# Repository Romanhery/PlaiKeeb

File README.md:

<h1>Plai-Keeb</h1>
Plai Keeb is a custom keyboard 75 % exploded keyboard with a rotary encoder and macro keys.
<h2>Features:</h2>
<ul>
   <li>Switched Rotary Encoder for volume control</li>
   <li>4 macro keys</li>
   <li>Candy Holder</li>
</ul>
<h2>PCB:</h2>
   <h2>Schematic</h2>
   
   <h2>PCB</h2>
   
   <p>Made in <a href="https://www.kicad.org/">Ki-CAD</a></p> 

<h2>CAD:</h2>
   <p>Everything is held together by using 6 M3 Bolts and heated inserts.</p>
   <p>It has 2 printed pieces and a plate to cover the electronics and house them.</p>
   <p>Made in Fusion 360</p>

<h2>Firmware:</h2>
   <p>Made with <a href="https://github.com/KMKfw/kmk_firmware">KMK</a> firmware</p> 
   <h3>Features</h3>
   <li>Volume control if you twist the rotary encoder and if you press the encoder to mute</li>
   <li>It has macros for any shorcut you want!</li>
   
<h2>BOM:</h2>
<p>Everything you need to make this macro pad is here!</p>
<ul>
    <li>9x Cherry MX Switches</li>
    <li>9x DSA Keycaps</li>
    <li>5x M3x5x4 Heatset inserts</li>
    <li>4x M3x16mm SHCS Bolts</li>
    <li>9x 1N4148 DO-35 Diodes.</li>
    <li>1x 0.91" OLED Display</li>
    <li>1x EC11 Rotary Encoder</li>
    <li>1x XIAO RP2040</li>
    <li>1x Case (2 printed parts)</li>
   <a href="https://docs.google.com/spreadsheets/d/1uIeMTGPOrdSAiFDxR4G393WpXhlTQVRrd_AwqsaPwl4/edit?usp=sharing">BOM HERE WITH LINKS</a>
</ul>
<h2>Acknowledgements</h2> 

* [Keeb](https://github.com/hackclub/hackpad/tree/main/cad/orpheuspad)
* [Void Pointer](https://github.com/Mirai-09/Keybie-Hackpads)
## Authors
- [@Romanhery](https://github.com/Romanhery)

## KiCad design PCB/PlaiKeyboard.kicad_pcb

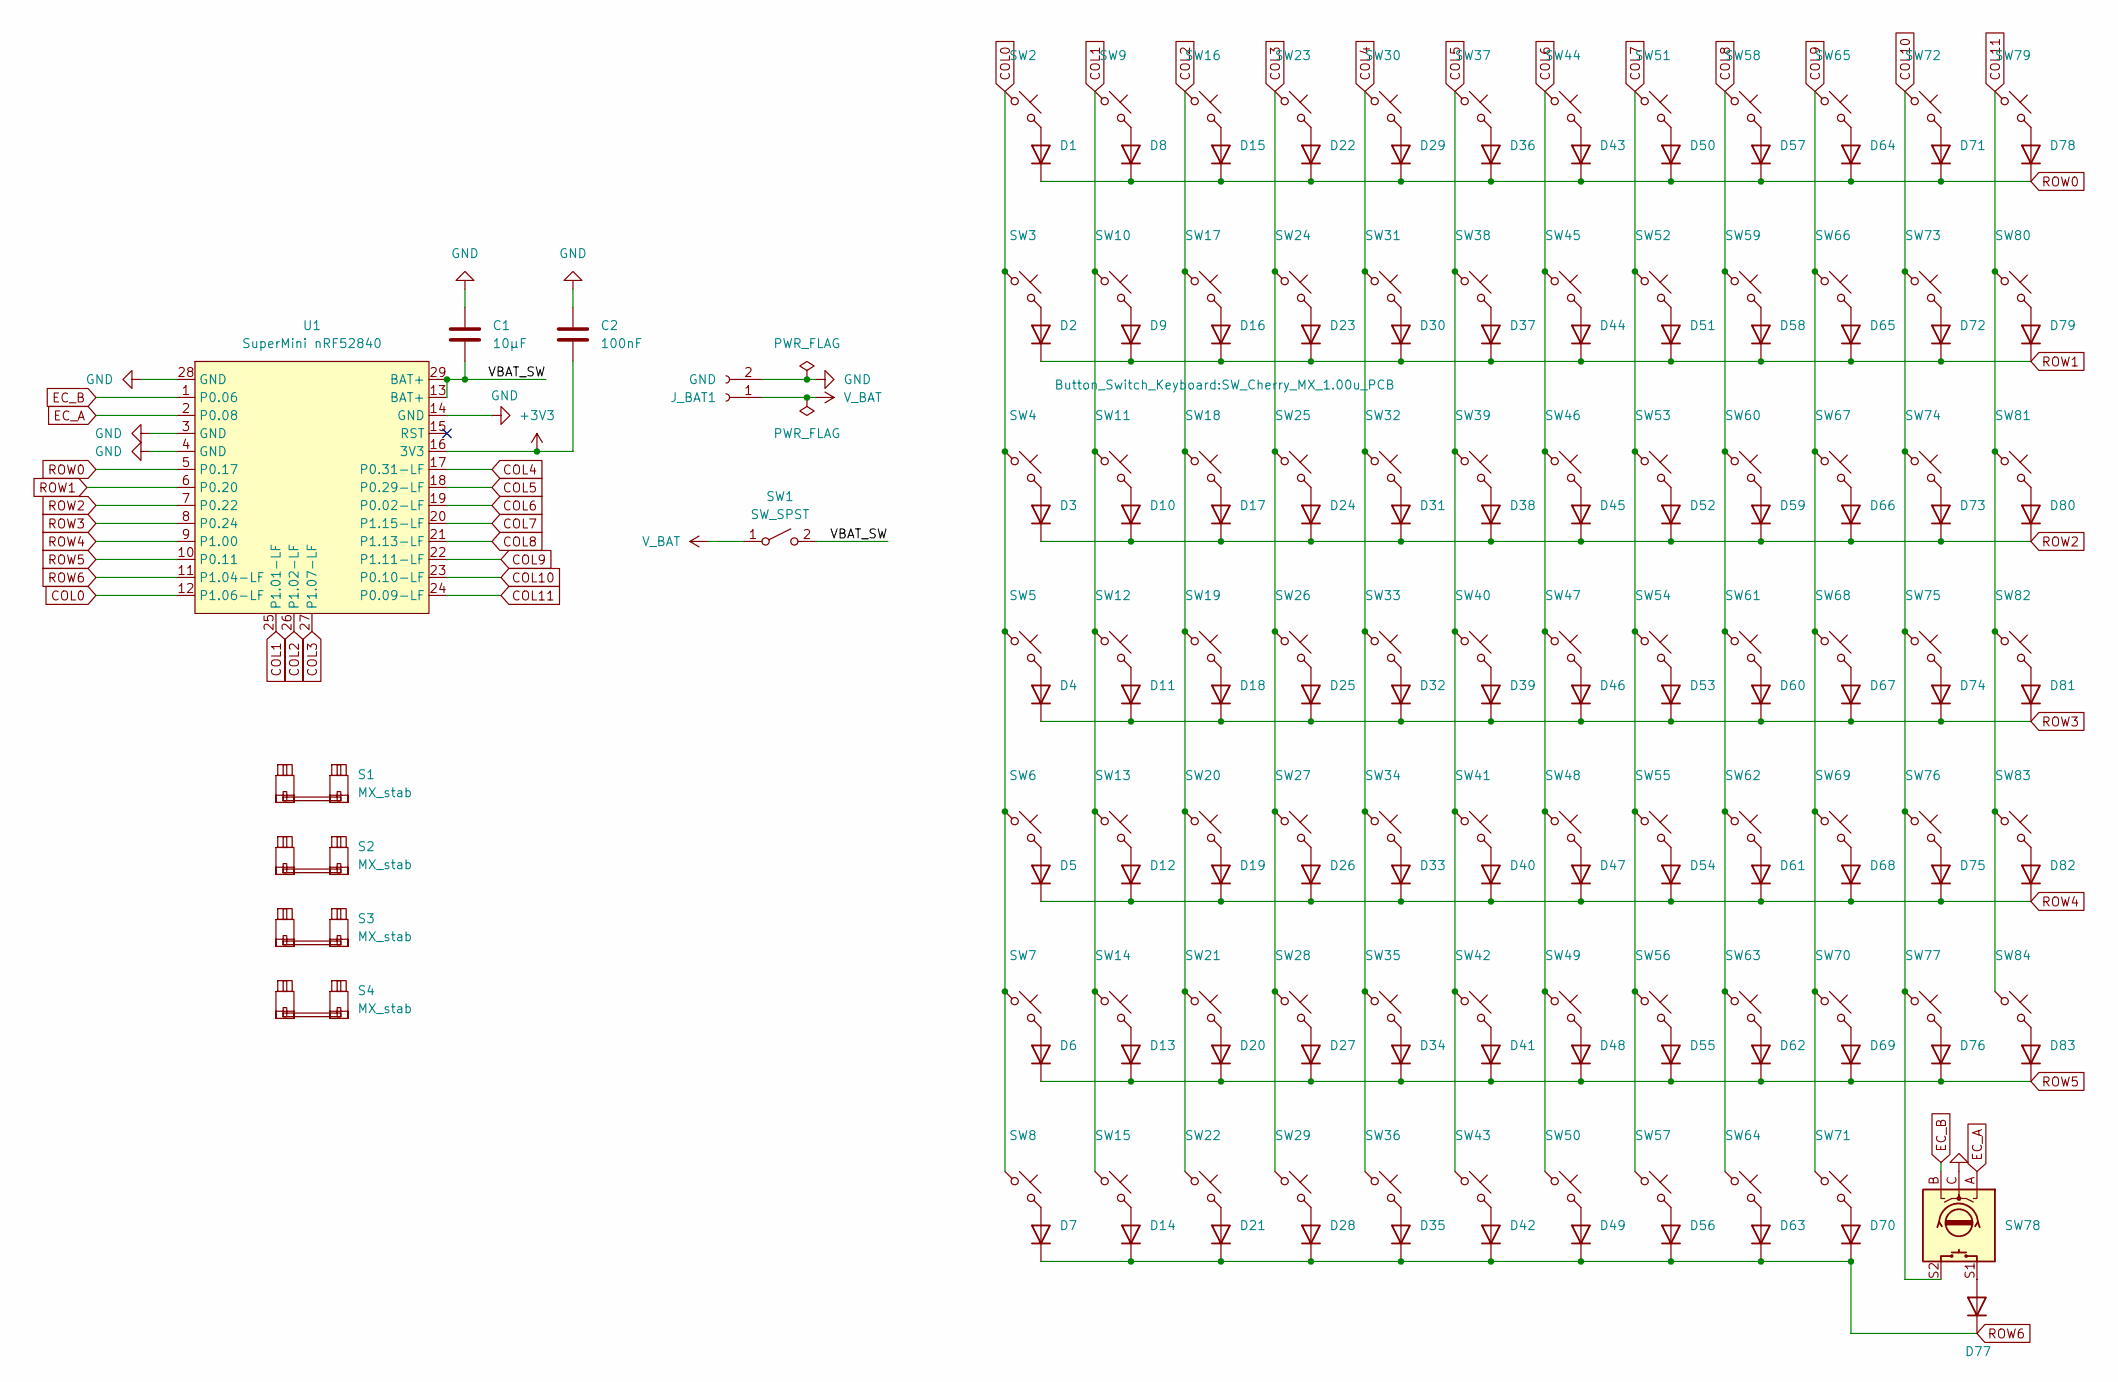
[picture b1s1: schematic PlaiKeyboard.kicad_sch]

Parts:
C1: 10µF; C_Disc_D4.7mm_W2.5mm_P5.00mm
C2: 100nF; C_Rect_L11.5mm_W5.2mm_P10.00mm_MKT
D1, D2, D3, D4, D5, D6, D7, D8, D9, D10, D11, D12, D13, D14, D15, D16, D17, D18, D19, D20, D21, D22, D23, D24, D25, D26, D27, D28, D29, D30, D31, D32, D33, D34, D35, D36, D37, D38, D39, D40, D41, D42, D43, D44, D45, D46, D47, D48, D49, D50, D51, D52, D53, D54, D55, D56, D57, D58, D59, D60, D61, D62, D63, D64, D65, D66, D67, D68, D69, D70, D71, D72, D73, D74, D75, D76, D77, D78, D79, D80, D81, D82, D83: 1N4148; D_DO-35_SOD27_P7.62mm_Horizontal
J_BAT1: GND; JST_PH_S2B-PH-K_1x02_P2.00mm_Horizontal
S1: MX_stab; STAB_MX_P_6.25u
S2, S3: MX_stab; STAB_MX_2.25u
S4: MX_stab; STAB_MX_2u
SW1: SW_SPST; 1P2T_SS-12D00_CNK
SW2, SW3, SW4, SW5, SW6, SW7, SW9, SW10, SW11, SW12, SW13, SW14, SW16, SW17, SW18, SW19, SW20, SW21, SW23, SW24, SW26, SW27, SW28, SW30, SW31, SW32, SW33, SW34, SW35, SW36, SW37, SW38, SW40, SW41, SW42, SW43, SW44, SW45, SW46, SW48, SW49, SW50, SW51, SW52, SW53, SW54, SW55, SW56, SW57, SW58, SW59, SW60, SW63, SW64, SW65, SW66, SW67, SW68, SW69, SW71, SW72, SW73, SW74, SW75, SW77, SW79, SW80, SW81, SW82, SW83, SW84: SW_Push_45deg; SW_Cherry_MX_1.00u_PCB
SW8, SW15, SW22: SW_Push_45deg; SW_Cherry_MX_1.25u_PCB
SW25: SW_Push_45deg; SW_Cherry_MX_2.00u_PCB
SW29: SW_Push_45deg; SW_Cherry_MX_6.25u_PCB
SW39, SW47: SW_Push_45deg; SW_Cherry_MX_1.50u_PCB
SW61, SW70: SW_Push_45deg; SW_Cherry_MX_1.75u_PCB
SW62, SW76: SW_Push_45deg; SW_Cherry_MX_2.25u_PCB
SW78: RotaryEncoder_Switch; RotaryEncoder_Alps_EC11E-Switch_Vertical_H20mm
U1: SuperMini nRF52840; SuperMini_nRF52840_AH_USBup

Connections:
+3V3: C2.1, U1.16 (3V3)
/VBAT_SW: C1.2, SW1.2 (B), U1.13 (BAT+), U1.29 (BAT+)
COL0: SW2.1, SW3.1, SW4.1, SW5.1, SW6.1, SW7.1, SW8.1, U1.12 (P1.06-LF)
COL1: SW9.1, SW10.1, SW11.1, SW12.1, SW13.1, SW14.1, SW15.1, U1.25 (P1.01-LF)
COL2: SW16.1, SW17.1, SW18.1, SW19.1, SW20.1, SW21.1, SW22.1, U1.26 (P1.02-LF)
COL3: SW23.1, SW24.1, SW25.1, SW26.1, SW27.1, SW28.1, SW29.1, U1.27 (P1.07-LF)
COL4: SW30.1, SW31.1, SW32.1, SW33.1, SW34.1, SW35.1, SW36.1, U1.17 (P0.31-LF)
COL5: SW37.1, SW38.1, SW39.1, SW40.1, SW41.1, SW42.1, SW43.1, U1.18 (P0.29-LF)
COL6: SW44.1, SW45.1, SW46.1, SW47.1, SW48.1, SW49.1, SW50.1, U1.19 (P0.02-LF)
COL7: SW51.1, SW52.1, SW53.1, SW54.1, SW55.1, SW56.1, SW57.1, U1.20 (P1.15-LF)
COL8: SW58.1, SW59.1, SW60.1, SW61.1, SW62.1, SW63.1, SW64.1, U1.21 (P1.13-LF)
COL9: SW65.1, SW66.1, SW67.1, SW68.1, SW69.1, SW70.1, SW71.1, U1.22 (P1.11-LF)
COL10: SW72.1, SW73.1, SW74.1, SW75.1, SW76.1, SW77.1, SW78.S2, U1.23 (P0.10-LF)
COL11: SW79.1, SW80.1, SW81.1, SW82.1, SW83.1, SW84.1, U1.24 (P0.09-LF)
EC_A: SW78.A, U1.2 (P0.08)
EC_B: SW78.B, U1.1 (P0.06)
GND: C1.1, C2.2, J_BAT1.2, SW78.C, U1.3 (GND), U1.4 (GND), U1.14 (GND), U1.28 (GND)
unnamed: D1.2 (A), SW2.2
unnamed: D2.2 (A), SW3.2
unnamed: D3.2 (A), SW4.2
unnamed: D4.2 (A), SW5.2
unnamed: D5.2 (A), SW6.2
unnamed: D6.2 (A), SW7.2
unnamed: D7.2 (A), SW8.2
unnamed: D8.2 (A), SW9.2
unnamed: D9.2 (A), SW10.2
unnamed: D10.2 (A), SW11.2
unnamed: D11.2 (A), SW12.2
unnamed: D12.2 (A), SW13.2
unnamed: D13.2 (A), SW14.2
unnamed: D14.2 (A), SW15.2
unnamed: D15.2 (A), SW16.2
unnamed: D16.2 (A), SW17.2
unnamed: D17.2 (A), SW18.2
unnamed: D18.2 (A), SW19.2
unnamed: D19.2 (A), SW20.2
unnamed: D20.2 (A), SW21.2
unnamed: D21.2 (A), SW22.2
unnamed: D22.2 (A), SW23.2
unnamed: D23.2 (A), SW24.2
unnamed: D24.2 (A), SW25.2
unnamed: D25.2 (A), SW26.2
unnamed: D26.2 (A), SW27.2
unnamed: D27.2 (A), SW28.2
unnamed: D28.2 (A), SW29.2
unnamed: D29.2 (A), SW30.2
unnamed: D30.2 (A), SW31.2
unnamed: D31.2 (A), SW32.2
unnamed: D32.2 (A), SW33.2
unnamed: D33.2 (A), SW34.2
unnamed: D34.2 (A), SW35.2
unnamed: D35.2 (A), SW36.2
unnamed: D36.2 (A), SW37.2
unnamed: D37.2 (A), SW38.2
unnamed: D38.2 (A), SW39.2
unnamed: D39.2 (A), SW40.2
unnamed: D40.2 (A), SW41.2
unnamed: D41.2 (A), SW42.2
unnamed: D42.2 (A), SW43.2
unnamed: D43.2 (A), SW44.2
unnamed: D44.2 (A), SW45.2
unnamed: D45.2 (A), SW46.2
unnamed: D46.2 (A), SW47.2
unnamed: D47.2 (A), SW48.2
unnamed: D48.2 (A), SW49.2
unnamed: D49.2 (A), SW50.2
unnamed: D50.2 (A), SW51.2
unnamed: D51.2 (A), SW52.2
unnamed: D52.2 (A), SW53.2
unnamed: D53.2 (A), SW54.2
unnamed: D54.2 (A), SW55.2
unnamed: D55.2 (A), SW56.2
unnamed: D56.2 (A), SW57.2
unnamed: D57.2 (A), SW58.2
unnamed: D58.2 (A), SW59.2
unnamed: D59.2 (A), SW60.2
unnamed: D60.2 (A), SW61.2
unnamed: D61.2 (A), SW62.2
unnamed: D62.2 (A), SW63.2
unnamed: D63.2 (A), SW64.2
unnamed: D64.2 (A), SW65.2
unnamed: D65.2 (A), SW66.2
unnamed: D66.2 (A), SW67.2
unnamed: D67.2 (A), SW68.2
unnamed: D68.2 (A), SW69.2
unnamed: D69.2 (A), SW70.2
unnamed: D70.2 (A), SW71.2
unnamed: D71.2 (A), SW72.2
unnamed: D72.2 (A), SW73.2
unnamed: D73.2 (A), SW74.2
unnamed: D74.2 (A), SW75.2
unnamed: D75.2 (A), SW76.2
unnamed: D76.2 (A), SW77.2
unnamed: D77.2 (A), SW78.S1
unnamed: D78.2 (A), SW79.2
unnamed: D79.2 (A), SW80.2
unnamed: D80.2 (A), SW81.2
unnamed: D81.2 (A), SW82.2
unnamed: D82.2 (A), SW83.2
unnamed: D83.2 (A), SW84.2
ROW0: D1.1 (K), D8.1 (K), D15.1 (K), D22.1 (K), D29.1 (K), D36.1 (K), D43.1 (K), D50.1 (K), D57.1 (K), D64.1 (K), D71.1 (K), D78.1 (K), U1.5 (P0.17)
ROW1: D2.1 (K), D9.1 (K), D16.1 (K), D23.1 (K), D30.1 (K), D37.1 (K), D44.1 (K), D51.1 (K), D58.1 (K), D65.1 (K), D72.1 (K), D79.1 (K), U1.6 (P0.20)
ROW2: D3.1 (K), D10.1 (K), D17.1 (K), D24.1 (K), D31.1 (K), D38.1 (K), D45.1 (K), D52.1 (K), D59.1 (K), D66.1 (K), D73.1 (K), D80.1 (K), U1.7 (P0.22)
ROW3: D4.1 (K), D11.1 (K), D18.1 (K), D25.1 (K), D32.1 (K), D39.1 (K), D46.1 (K), D53.1 (K), D60.1 (K), D67.1 (K), D74.1 (K), D81.1 (K), U1.8 (P0.24)
ROW4: D5.1 (K), D12.1 (K), D19.1 (K), D26.1 (K), D33.1 (K), D40.1 (K), D47.1 (K), D54.1 (K), D61.1 (K), D68.1 (K), D75.1 (K), D82.1 (K), U1.9 (P1.00)
ROW5: D6.1 (K), D13.1 (K), D20.1 (K), D27.1 (K), D34.1 (K), D41.1 (K), D48.1 (K), D55.1 (K), D62.1 (K), D69.1 (K), D76.1 (K), D83.1 (K), U1.10 (P0.11)
ROW6: D7.1 (K), D14.1 (K), D21.1 (K), D28.1 (K), D35.1 (K), D42.1 (K), D49.1 (K), D56.1 (K), D63.1 (K), D70.1 (K), D77.1 (K), U1.11 (P1.04-LF)
V_BAT: J_BAT1.1, SW1.1 (A)

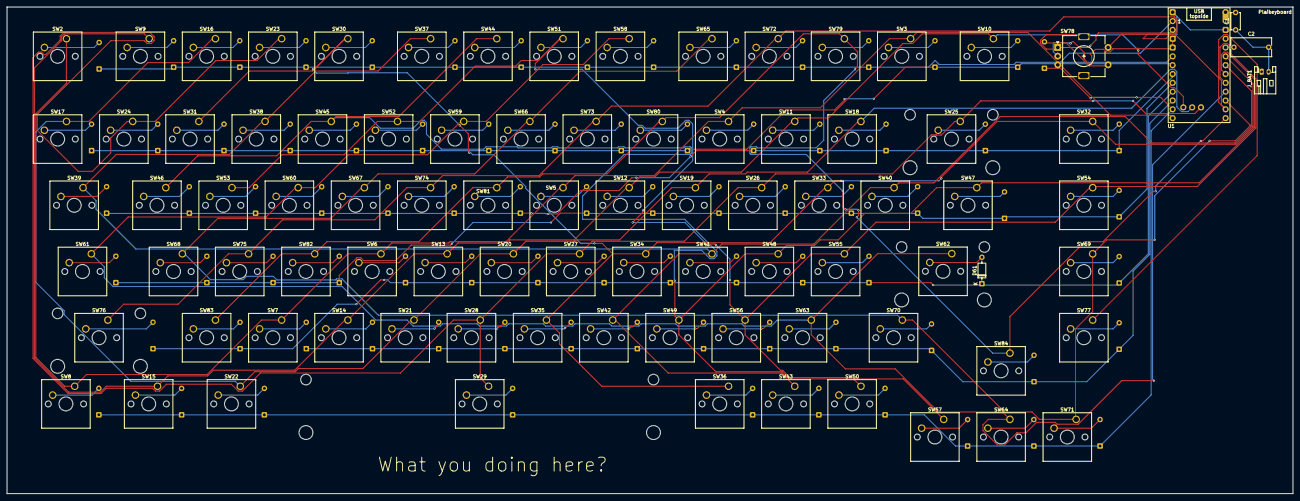
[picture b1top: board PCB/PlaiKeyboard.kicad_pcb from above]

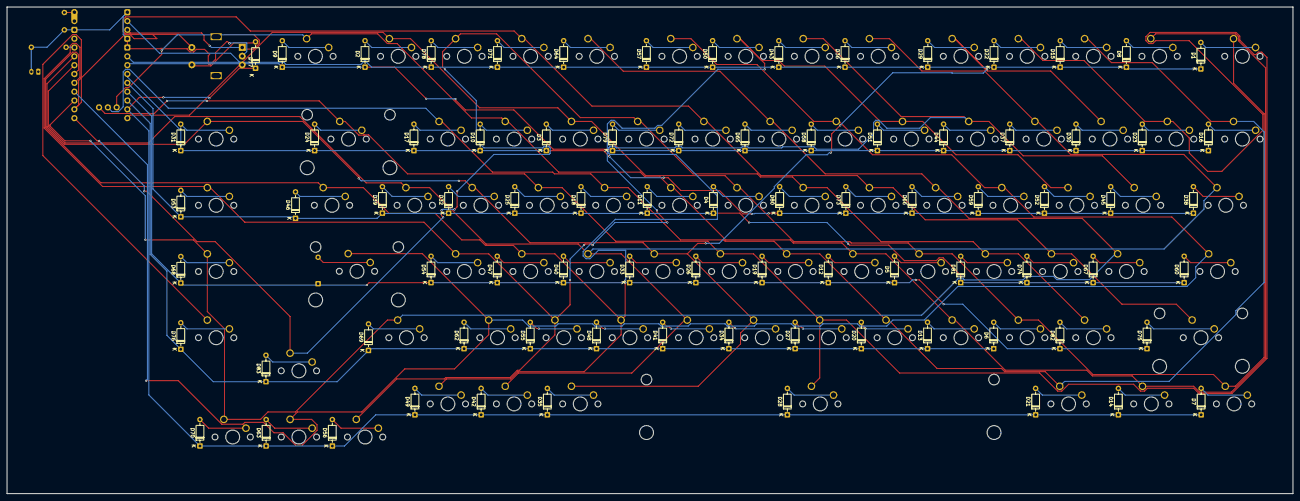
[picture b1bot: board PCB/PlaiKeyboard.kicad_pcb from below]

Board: 2 copper layers, 370.0 x 140.0 mm, 170 parts (82 on the bottom side), 107 nets.

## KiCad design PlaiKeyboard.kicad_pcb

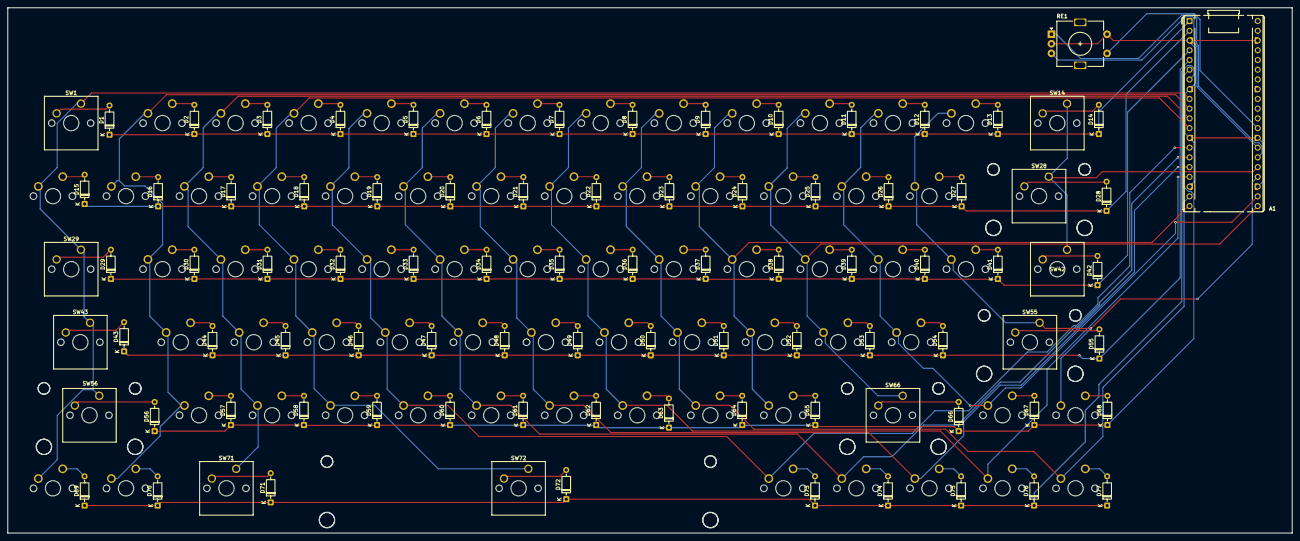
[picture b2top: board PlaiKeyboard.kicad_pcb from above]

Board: 2 copper layers, 335.0 x 137.0 mm, 161 parts (0 on the bottom side), 101 nets.

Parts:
A1: RaspberryPi_Pico; RaspberryPi_Pico_Common_THT
D1, D2, D3, D4, D5, D6, D7, D8, D9, D10, D11, D12, D13, D14, D15, D16, D17, D18, D19, D20, D21, D22, D23, D24, D25, D26, D27, D28, D29, D30, D31, D32, D33, D34, D35, D36, D37, D38, D39, D40, D41, D42, D43, D44, D45, D46, D47, D48, D49, D50, D51, D52, D53, D54, D55, D56, D57, D58, D59, D60, D61, D62, D63, D64, D65, D66, D67, D68, D69, D70, D71, D72, D73, D74, D75, D76, D77: 1N4148; D_DO-35_SOD27_P7.62mm_Horizontal
RE1: RotaryEncoder_Switch; RotaryEncoder_Alps_EC11E-Switch_Vertical_H20mm
S1, S2, S3: MX_stab; STAB_MX_2u
S4: MX_stab; STAB_MX_2.25u
S5: MX_stab; STAB_MX_6.25u
SW1, SW14, SW29, SW42: SW_Push_45deg; SW_Cherry_MX_1.50u_PCB
SW2, SW3, SW4, SW5, SW6, SW7, SW8, SW9, SW10, SW11, SW12, SW13, SW15, SW16, SW17, SW18, SW19, SW20, SW21, SW22, SW23, SW24, SW25, SW26, SW27, SW30, SW31, SW32, SW33, SW34, SW35, SW36, SW37, SW38, SW39, SW40, SW41, SW44, SW45, SW46, SW47, SW48, SW49, SW50, SW51, SW52, SW53, SW54, SW57, SW58, SW59, SW60, SW61, SW62, SW63, SW64, SW65, SW67, SW68, SW69, SW70, SW73, SW74, SW75, SW76, SW77: SW_Push_45deg; SW_MX_1u
SW28, SW56, SW66: SW_Push_45deg; SW_Cherry_MX_2.00u_PCB
SW43, SW71: SW_Push_45deg; SW_Cherry_MX_1.75u_PCB
SW55: SW_Push_45deg; SW_Cherry_MX_2.25u_PCB
SW72: SW_Push_45deg; SW_Cherry_MX_6.25u_PCB

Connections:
A_20: A1.26 (GPIO20), RE1.A
B_21: A1.27 (GPIO21), RE1.B
COL0: A1.9 (GPIO6), SW1.1, SW15.1, SW29.1, SW43.1, SW56.1, SW69.1
COL1: A1.10 (GPIO7), SW2.1, SW16.1, SW30.1, SW44.1, SW57.1, SW70.1
COL2: A1.11 (GPIO8), SW3.1, SW17.1, SW31.1, SW45.1, SW58.1, SW71.1
COL3: A1.12 (GPIO9), SW4.1, SW18.1, SW32.1, SW46.1, SW59.1, SW72.1
COL4: A1.14 (GPIO10), SW5.1, SW19.1, SW33.1, SW47.1, SW60.1, SW73.1
COL5: A1.15 (GPIO11), SW6.1, SW20.1, SW34.1, SW48.1, SW61.1, SW74.1
COL6: A1.16 (GPIO12), SW7.1, SW21.1, SW35.1, SW49.1, SW62.1, SW75.1
COL7: A1.17 (GPIO13), SW8.1, SW22.1, SW36.1, SW50.1, SW63.1, SW76.1
COL8: A1.19 (GPIO14), SW9.1, SW23.1, SW37.1, SW51.1, SW64.1, SW77.1
COL9: A1.20 (GPIO15), SW10.1, SW24.1, SW38.1, SW52.1, SW65.1
COL10: A1.21 (GPIO16), SW11.1, SW25.1, SW39.1, SW53.1, SW66.1
COL11: A1.22 (GPIO17), SW12.1, SW26.1, SW40.1, SW54.1, SW67.1
COL12: A1.24 (GPIO18), SW13.1, SW27.1, SW41.1, SW55.1, SW68.1
COL13: A1.25 (GPIO19), SW14.1, SW28.1, SW42.1
GND: A1.3 (GND), A1.8 (GND), A1.13 (GND), A1.18 (GND), A1.23 (GND), A1.28 (GND), A1.38 (GND), RE1.C, RE1.S2
unnamed: D1.2 (A), SW1.2
unnamed: D2.2 (A), SW2.2
unnamed: D3.2 (A), SW3.2
unnamed: D4.2 (A), SW4.2
unnamed: D5.2 (A), SW5.2
unnamed: D6.2 (A), SW6.2
unnamed: D7.2 (A), SW7.2
unnamed: D8.2 (A), SW8.2
unnamed: D9.2 (A), SW9.2
unnamed: D10.2 (A), SW10.2
unnamed: D11.2 (A), SW11.2
unnamed: D12.2 (A), SW12.2
unnamed: D13.2 (A), SW13.2
unnamed: D14.2 (A), SW14.2
unnamed: D15.2 (A), SW15.2
unnamed: D16.2 (A), SW16.2
unnamed: D17.2 (A), SW17.2
unnamed: D18.2 (A), SW18.2
unnamed: D19.2 (A), SW19.2
unnamed: D20.2 (A), SW20.2
unnamed: D21.2 (A), SW21.2
unnamed: D22.2 (A), SW22.2
unnamed: D23.2 (A), SW23.2
unnamed: D24.2 (A), SW24.2
unnamed: D25.2 (A), SW25.2
unnamed: D26.2 (A), SW26.2
unnamed: D27.2 (A), SW27.2
unnamed: D28.2 (A), SW28.2
unnamed: D29.2 (A), SW29.2
unnamed: D30.2 (A), SW30.2
unnamed: D31.2 (A), SW31.2
unnamed: D32.2 (A), SW32.2
unnamed: D33.2 (A), SW33.2
unnamed: D34.2 (A), SW34.2
unnamed: D35.2 (A), SW35.2
unnamed: D36.2 (A), SW36.2
unnamed: D37.2 (A), SW37.2
unnamed: D38.2 (A), SW38.2
unnamed: D39.2 (A), SW39.2
unnamed: D40.2 (A), SW40.2
unnamed: D41.2 (A), SW41.2
unnamed: D42.2 (A), SW42.2
unnamed: D43.2 (A), SW43.2
unnamed: D44.2 (A), SW44.2
unnamed: D45.2 (A), SW45.2
unnamed: D46.2 (A), SW46.2
unnamed: D47.2 (A), SW47.2
unnamed: D48.2 (A), SW48.2
unnamed: D49.2 (A), SW49.2
unnamed: D50.2 (A), SW50.2
unnamed: D51.2 (A), SW51.2
unnamed: D52.2 (A), SW52.2
unnamed: D53.2 (A), SW53.2
unnamed: D54.2 (A), SW54.2
unnamed: D55.2 (A), SW55.2
unnamed: D56.2 (A), SW56.2
unnamed: D57.2 (A), SW57.2
unnamed: D58.2 (A), SW58.2
unnamed: D59.2 (A), SW59.2
unnamed: D60.2 (A), SW60.2
unnamed: D61.2 (A), SW61.2
unnamed: D62.2 (A), SW62.2
unnamed: D63.2 (A), SW63.2
unnamed: D64.2 (A), SW64.2
unnamed: D65.2 (A), SW65.2
unnamed: D66.2 (A), SW66.2
unnamed: D67.2 (A), SW67.2
unnamed: D68.2 (A), SW68.2
unnamed: D69.2 (A), SW69.2
unnamed: D70.2 (A), SW70.2
unnamed: D71.2 (A), SW71.2
unnamed: D72.2 (A), SW72.2
unnamed: D73.2 (A), SW73.2
unnamed: D74.2 (A), SW74.2
unnamed: D75.2 (A), SW75.2
unnamed: D76.2 (A), SW76.2
unnamed: D77.2 (A), SW77.2
ROW0: A1.1 (GPIO0), D1.1 (K), D2.1 (K), D3.1 (K), D4.1 (K), D5.1 (K), D6.1 (K), D7.1 (K), D8.1 (K), D9.1 (K), D10.1 (K), D11.1 (K), D12.1 (K), D13.1 (K), D14.1 (K)
ROW1: A1.2 (GPIO1), D15.1 (K), D16.1 (K), D17.1 (K), D18.1 (K), D19.1 (K), D20.1 (K), D21.1 (K), D22.1 (K), D23.1 (K), D24.1 (K), D25.1 (K), D26.1 (K), D27.1 (K), D28.1 (K)
ROW2: A1.4 (GPIO2), D29.1 (K), D30.1 (K), D31.1 (K), D32.1 (K), D33.1 (K), D34.1 (K), D35.1 (K), D36.1 (K), D37.1 (K), D38.1 (K), D39.1 (K), D40.1 (K), D41.1 (K), D42.1 (K)
ROW3: A1.5 (GPIO3), D43.1 (K), D44.1 (K), D45.1 (K), D46.1 (K), D47.1 (K), D48.1 (K), D49.1 (K), D50.1 (K), D51.1 (K), D52.1 (K), D53.1 (K), D54.1 (K), D55.1 (K)
ROW4: A1.6 (GPIO4), D56.1 (K), D57.1 (K), D58.1 (K), D59.1 (K), D60.1 (K), D61.1 (K), D62.1 (K), D63.1 (K), D64.1 (K), D65.1 (K), D66.1 (K), D67.1 (K), D68.1 (K)
ROW5: A1.7 (GPIO5), D69.1 (K), D70.1 (K), D71.1 (K), D72.1 (K), D73.1 (K), D74.1 (K), D75.1 (K), D76.1 (K), D77.1 (K)
S1_22: A1.29 (GPIO22), RE1.S1
